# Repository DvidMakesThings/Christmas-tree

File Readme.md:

# Christmas Tree Project

## Contents
This folder contains all the documents related to the Christmas Tree project.

## Usage
To use the files in this project, navigate to the respective directories and follow the instructions provided in each document.

## License
This project is licensed under the MIT License.

## Contact
For any questions or feedback, please contact:
- Email: [s.dvid@hotmail.com](mailto:s.dvid@hotmail.com)
- GitHub: [DvidMakesThings](https://github.com/DvidMakesThings)

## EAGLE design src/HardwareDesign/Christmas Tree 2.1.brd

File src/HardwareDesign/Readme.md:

# # Christmas Tree Project Hardware Design Files

## Contents
This folder contains the hardware design files for the Christmas Tree project. The main components include:
- Schematic diagrams
- PCB layouts
- Bill of Materials (BOM)
- Gerber files

## Usage
To use these hardware design files:
1. Open the schematic diagrams and PCB layouts using EAGLE software.
2. Review the Bill of Materials for required components.
3. Follow the design files to assemble and test the hardware.
4. Use the Gerber files for PCB manufacturing.

## License
This project is licensed under the MIT License.

## Contact
For any questions or feedback, please contact:
- Email: [s.dvid@hotmail.com](mailto:s.dvid@hotmail.com)
- GitHub: [DvidMakesThings](https://github.com/DvidMakesThings)

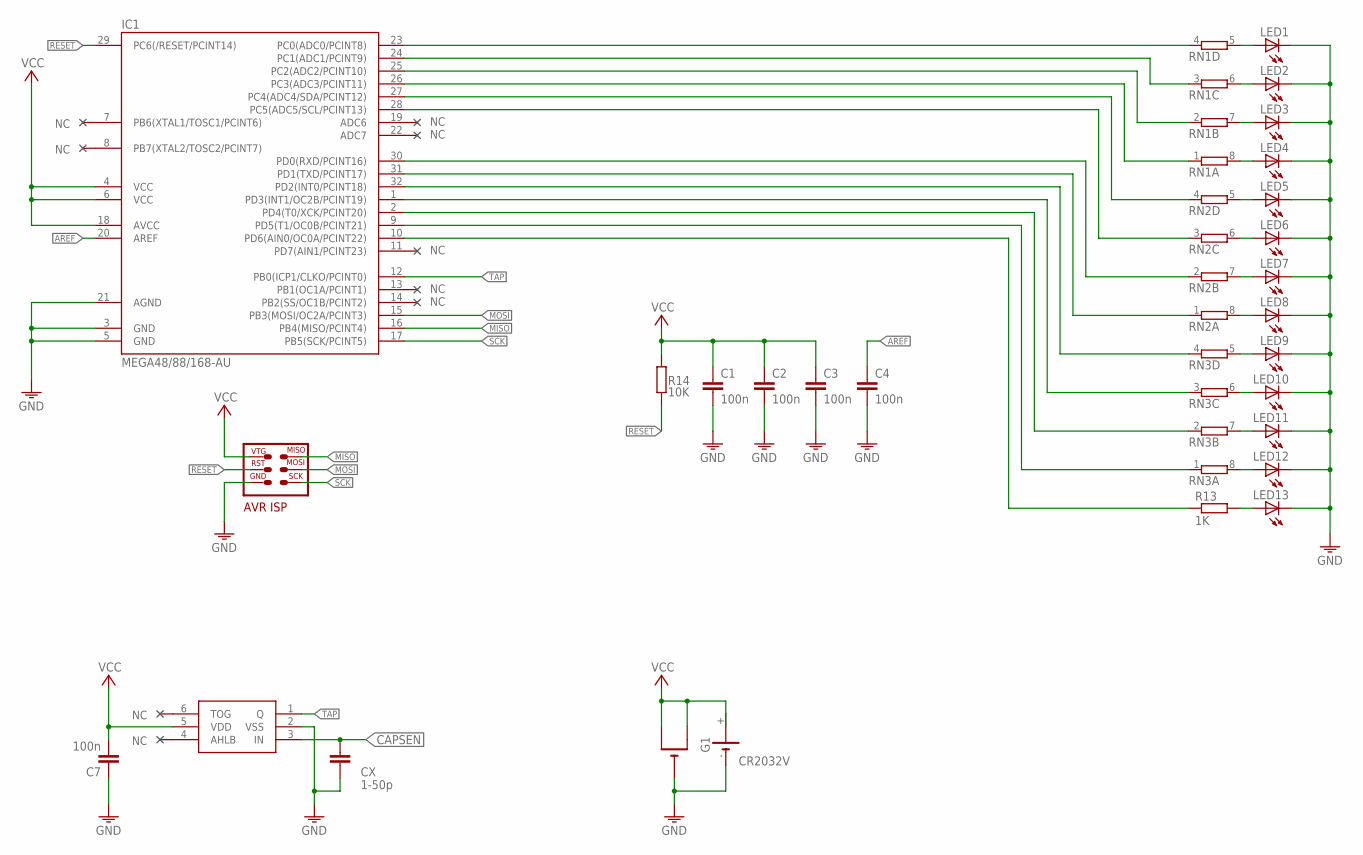
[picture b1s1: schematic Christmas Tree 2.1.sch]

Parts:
BAT: CR2032SMT; CR2032-SMD
C1, C2, C3, C4, C7: 100n; C0402K
CX: 1-50p; C0402K
G1: CR2032V
IC1: MEGA48/88/168-AU; TQFP32-08
LED1, LED2, LED3, LED4, LED5, LED6, LED7, LED8, LED9, LED10, LED11, LED12, LED13: LEDCHIPLED_0805; CHIPLED_0805
R13: 1K; R0402
R14: 10K; R0402
RN1, RN2, RN3: 4R-N0603-ARC; 0603-ARC
TTP223E1: TTP223E; SOT23-6
U$12: ISP

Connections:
AREF: C4.1, IC1.20 (AREF)
CAPSEN: CX.2, TTP223E1.3 (IN)
GND: BAT.-, C1.2, C2.2, C3.2, C4.2, C7.1, CX.1, G1.-, IC1.3 (GND), IC1.5 (GND), IC1.21 (AGND), LED1.C, LED2.C, LED3.C, LED4.C, LED5.C, LED6.C, LED7.C, LED8.C, LED9.C, LED10.C, LED11.C, LED12.C, LED13.C, TTP223E1.2 (VSS), U$12.6
MISO: IC1.16 (PB4(MISO/PCINT4)), U$12.1
MOSI: IC1.15 (PB3(MOSI/OC2A/PCINT3)), U$12.4
unnamed: LED1.A, RN1.5 (2)
unnamed: LED2.A, RN1.6 (2)
unnamed: LED3.A, RN1.7 (2)
unnamed: LED4.A, RN1.8 (2)
unnamed: LED5.A, RN2.5 (2)
unnamed: LED6.A, RN2.6 (2)
unnamed: LED7.A, RN2.7 (2)
unnamed: LED8.A, RN2.8 (2)
unnamed: LED9.A, RN3.5 (2)
unnamed: LED10.A, RN3.6 (2)
unnamed: LED11.A, RN3.7 (2)
unnamed: LED12.A, RN3.8 (2)
unnamed: LED13.A, R13.2
unnamed: IC1.23 (PC0(ADC0/PCINT8)), RN1.4 (1)
unnamed: IC1.24 (PC1(ADC1/PCINT9)), RN1.3 (1)
unnamed: IC1.25 (PC2(ADC2/PCINT10)), RN1.2 (1)
unnamed: IC1.26 (PC3(ADC3/PCINT11)), RN1.1
unnamed: IC1.27 (PC4(ADC4/SDA/PCINT12)), RN2.4 (1)
unnamed: IC1.28 (PC5(ADC5/SCL/PCINT13)), RN2.3 (1)
unnamed: IC1.30 (PD0(RXD/PCINT16)), RN2.2 (1)
unnamed: IC1.31 (PD1(TXD/PCINT17)), RN2.1
unnamed: IC1.32 (PD2(INT0/PCINT18)), RN3.4 (1)
unnamed: IC1.1 (PD3(INT1/OC2B/PCINT19)), RN3.3 (1)
unnamed: IC1.2 (PD4(T0/XCK/PCINT20)), RN3.2 (1)
unnamed: IC1.9 (PD5(T1/OC0B/PCINT21)), RN3.1
unnamed: IC1.10 (PD6(AIN0/OC0A/PCINT22)), R13.1
RESET: IC1.29 (PC6(/RESET/PCINT14)), R14.1, U$12.5
SCK: IC1.17 (PB5(SCK/PCINT5)), U$12.3
TAP: IC1.12 (PB0(ICP1/CLKO/PCINT0)), TTP223E1.1 (Q)
VCC: BAT.+$1 (+), BAT.+$2 (+1), C1.1, C2.1, C3.1, C7.2, G1.+, G1.+@1 (+), IC1.4 (VCC), IC1.6 (VCC), IC1.18 (AVCC), R14.2, TTP223E1.5 (VDD), U$12.2

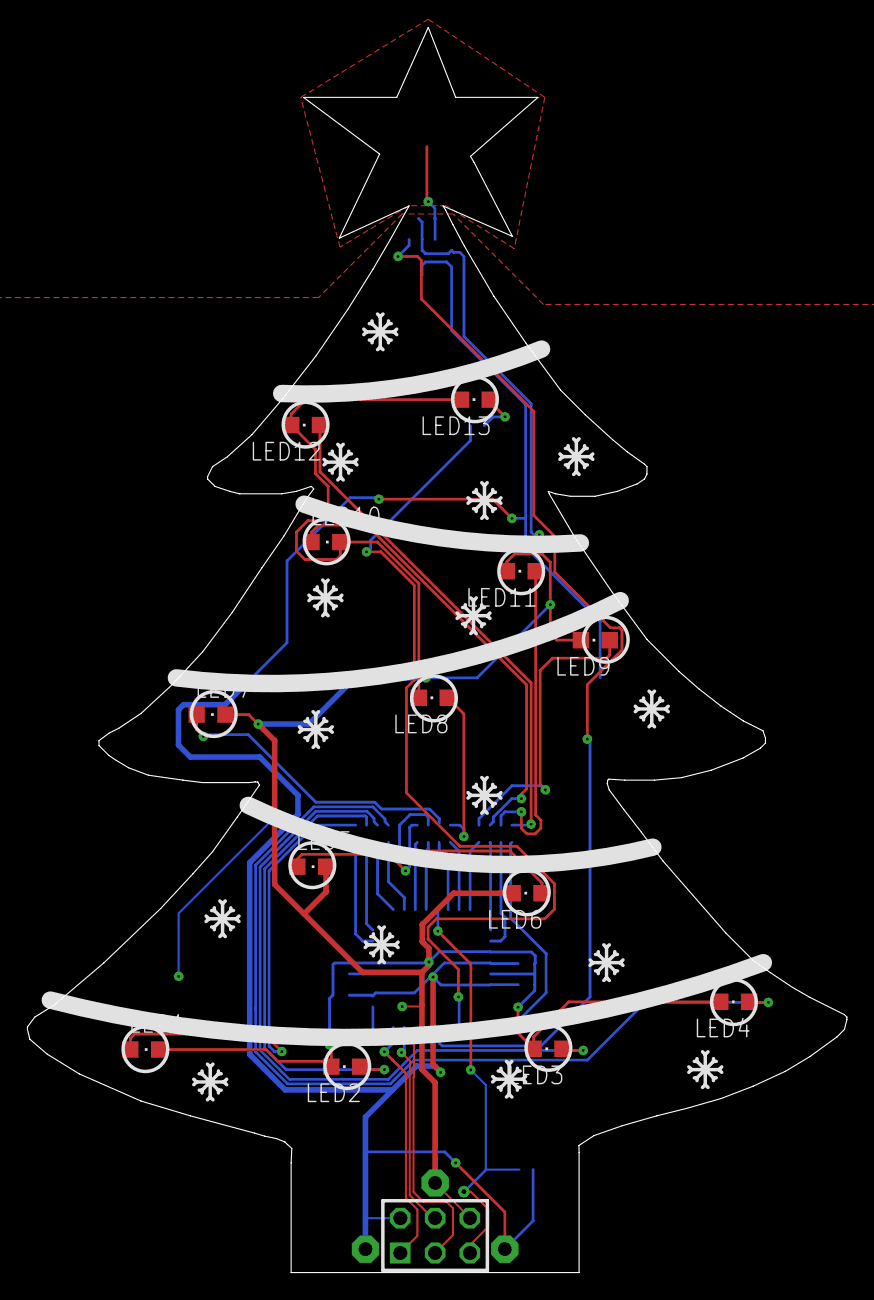
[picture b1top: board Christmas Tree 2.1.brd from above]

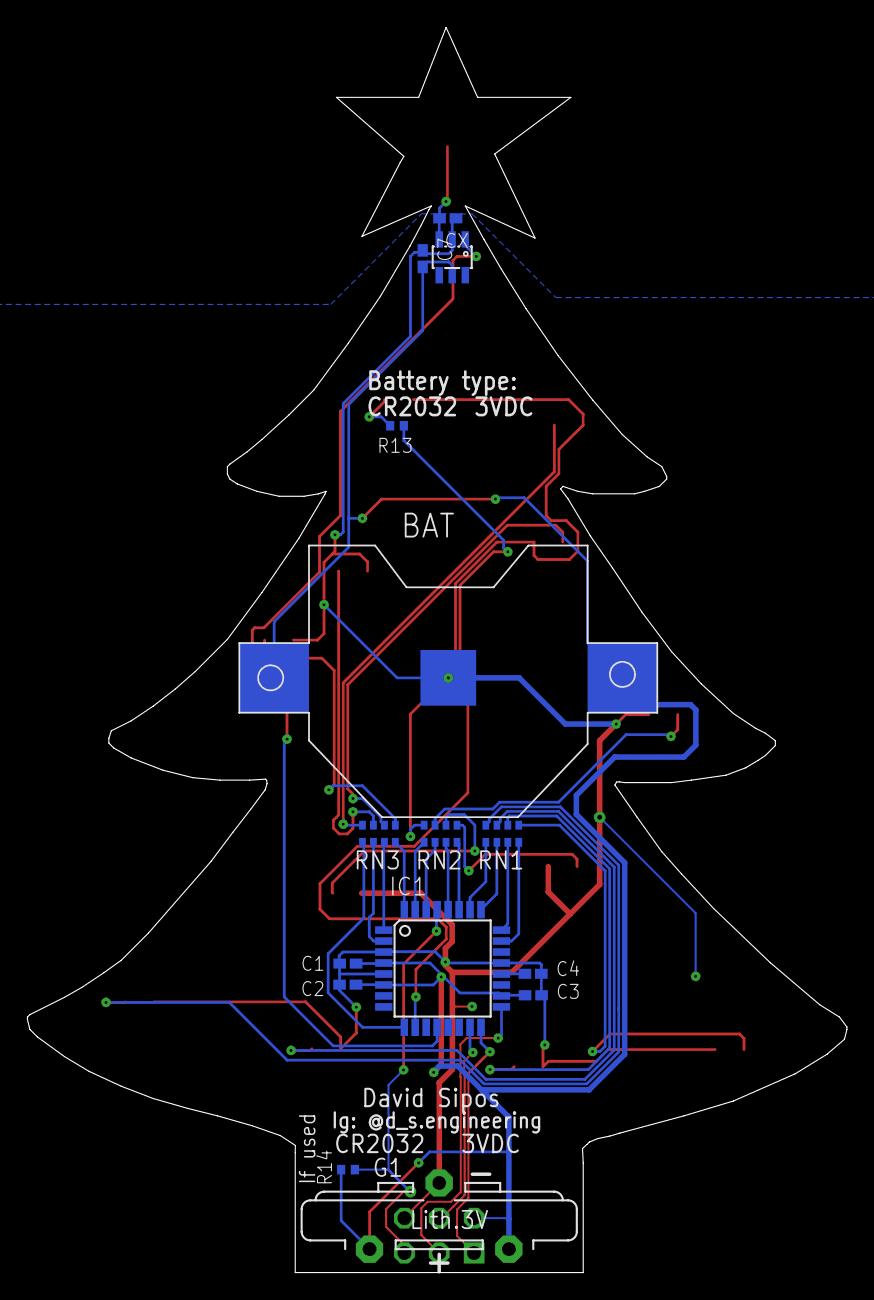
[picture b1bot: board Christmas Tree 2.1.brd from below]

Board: 2 copper layers, 59.8 x 90.8 mm, 29 parts (15 on the bottom side), 35 nets.

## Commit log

2024-11-24 initial creation
